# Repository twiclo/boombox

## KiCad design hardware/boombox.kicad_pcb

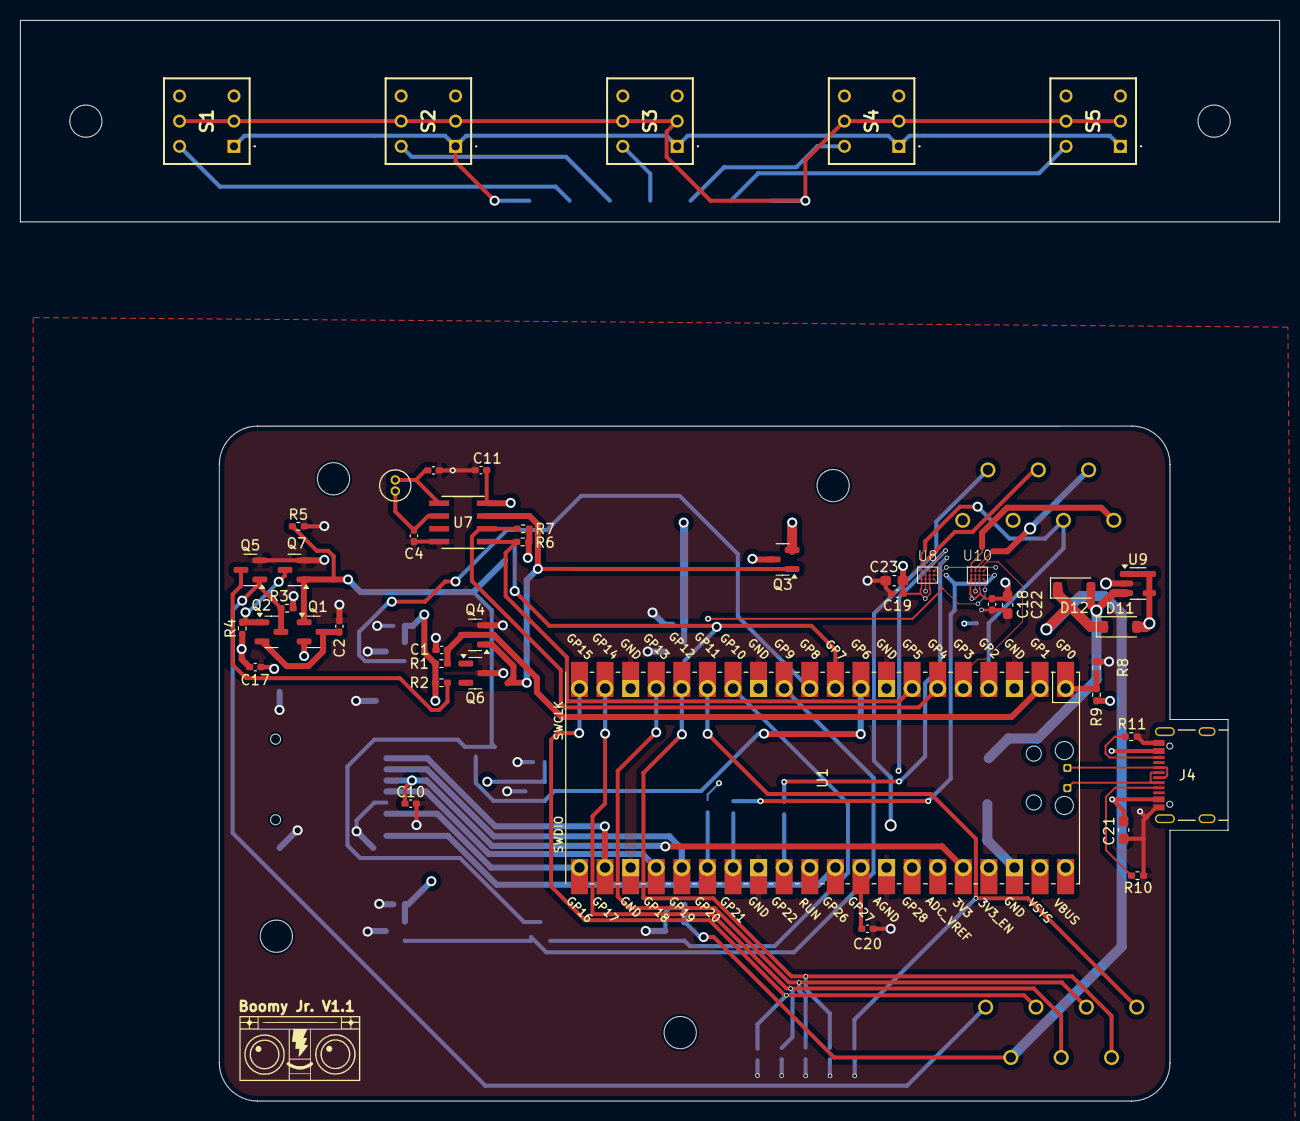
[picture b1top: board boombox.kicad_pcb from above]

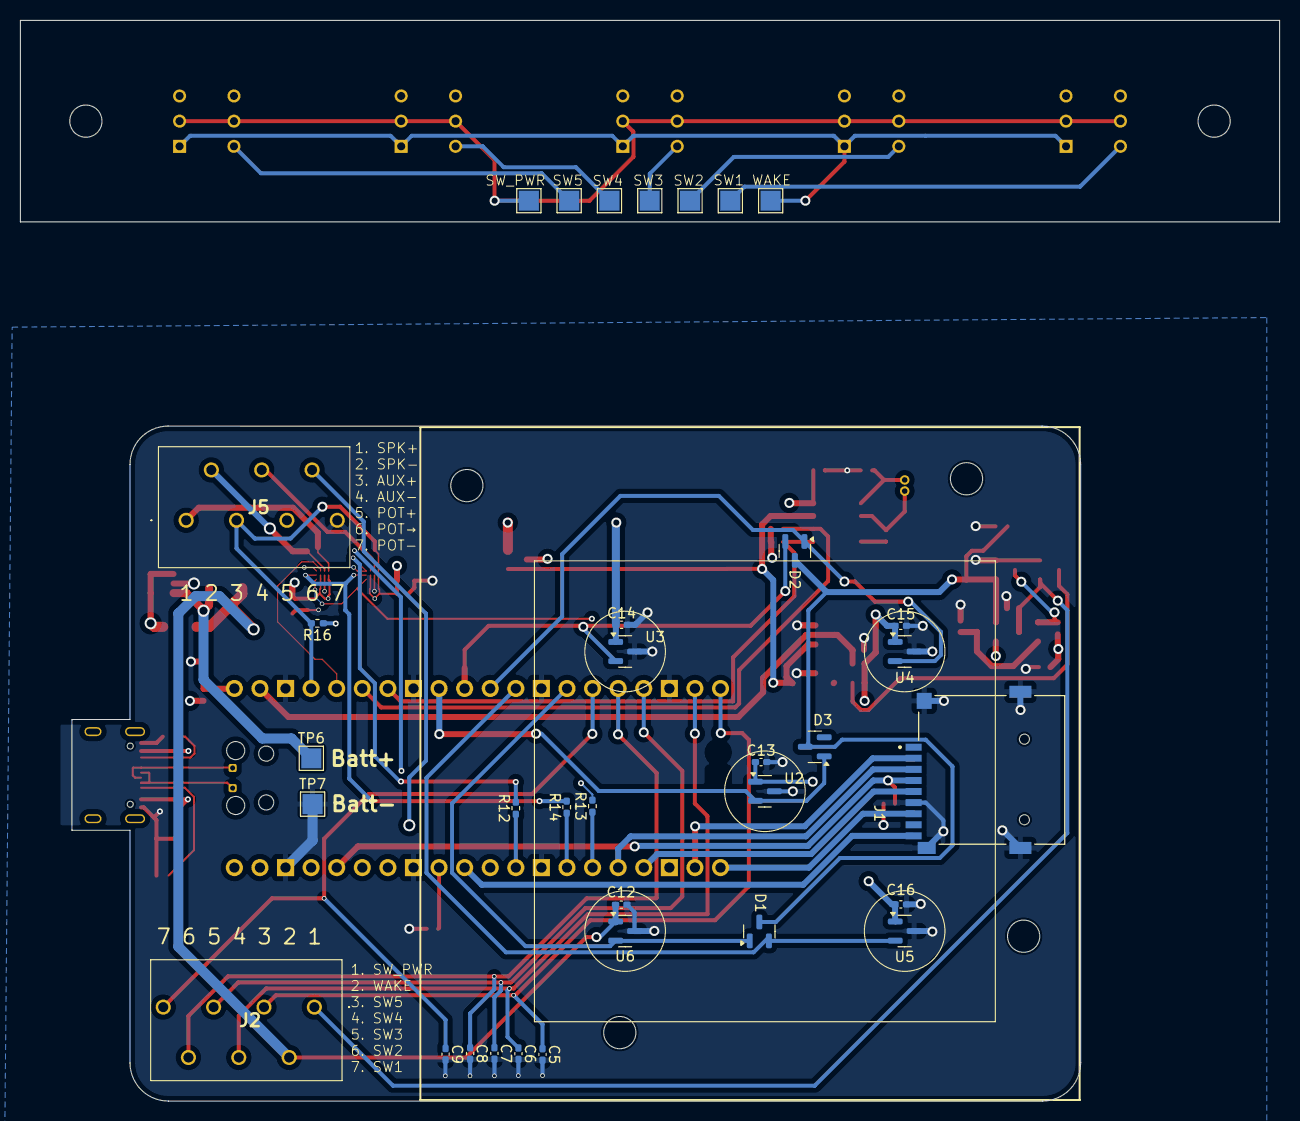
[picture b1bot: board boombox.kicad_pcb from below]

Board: 4 copper layers, 125.0 x 107.3 mm, 79 parts (34 on the bottom side), 56 nets.

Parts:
C1, C3, C4: 6pF; C_0402_1005Metric_Pad0.74x0.62mm_HandSolder
C2: 1nF; C_0402_1005Metric_Pad0.74x0.62mm_HandSolder
C5, C6, C7, C8, C9: 0.1u; C_0402_1005Metric_Pad0.74x0.62mm_HandSolder
C10, C11, C12, C13, C14, C15, C16, C17, C18, C19, C20: 0.1uF; C_0402_1005Metric_Pad0.74x0.62mm_HandSolder
C21, C22, C23: 10uF; C_0603_1608Metric_Pad1.08x0.95mm_HandSolder
D1, D2, D3: D_Dual_CommonCathode_AAK_Split; SOT-23
D11, D12: D_Schottky; D_SOD-123
J1: Micro_SD_Card_Det1; CUI_MSD-4-A
J2, J5: Screw_Terminal_01x07; 1990054
J4: USB_C_Receptacle_USB2.0_16P; CUI_UJ20-C-H-C-4-SMT-TR
Q1, Q2, Q3, Q4, Q5, Q6, Q7: SOT-23
R1, R2, R3, R4, R5, R16: 1M; R_0402_1005Metric_Pad0.72x0.64mm_HandSolder
R6, R7, R8, R9: 10k; R_0402_1005Metric_Pad0.72x0.64mm_HandSolder
R10, R11: 5.1k; R_0402_1005Metric_Pad0.72x0.64mm_HandSolder
R12, R13, R14: 0; R_0402_1005Metric_Pad0.72x0.64mm_HandSolder
S1, S2, S3, S4, S5: TL2202OAYA
TP1, TP2, TP3, TP4, TP5, TP6, TP7, TP8, TP12: TestPoint_Small; TestPoint_Pad_2.0x2.0mm
U1: Pico; RPi_Pico_SMD_TH
U2, U3, U4, U5, U6: TMAG5231; SOT-23
U7: MCP7940MT-I/SN; SOIC8-N_MC_MCH
U8, U10: MAX98365A; MAX98365
U9: MCP73811T-420I-OT; SOT-23-5
Y1: Crystal; XTAL_ECS-.327-6-13X

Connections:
/Audio/HEADPHONE_EN: U1.34 (GPIO28_ADC2), U8.A3 (EN)
/Audio/I2S_BCLK: R12.1, U1.29 (GPIO22)
/Audio/I2S_DOUT: R14.1, U1.27 (GPIO21)
/Audio/I2S_LRCLK: R13.1, U1.26 (GPIO20)
/Audio/SPEAKER_EN: U1.5 (GPIO3), U10.A3 (EN)
/Audio/VOL: C20.1, J5.6, U1.32 (GPIO27_ADC1)
/Audio/~HEADPHONE_DETECT: J5.3, R16.2, U1.4 (GPIO2), U8.A1 (OUTP)
/Power/BTN_LATCH: J2.1, Q2.3 (D), Q5.1 (G), R3.1
/Power/CLOCK_ALARM: Q3.1 (G), Q4.1 (G), Q5.3 (D), Q6.3 (D), R2.2, U7.7 (MFP)
/Power/MAG_SENSOR0: D3.1 (A), U1.9 (GPIO6), U2.2 (OUT)
/Power/MAG_SENSOR1: D2.2 (A), U1.10 (GPIO7), U3.2 (OUT)
/Power/MAG_SENSOR2: D2.1 (A), U1.11 (GPIO8), U4.2 (OUT)
/Power/MAG_SENSOR3: D1.2 (A), U1.12 (GPIO9), U5.2 (OUT)
/Power/MAG_SENSOR4: D1.1 (A), U1.14 (GPIO10), U6.2 (OUT)
/Power/POWER IN: C21.1, D11.2 (A), J4.A4 (VBUS), J4.A9 (VBUS), J4.B4 (VBUS), J4.B9 (VBUS), R9.2, U9.1 (CE), U9.4 (V_{DD}), U9.5 (PROG)
/Power/~POWER_OFF: C1.1, Q4.3 (D), Q6.1 (G), R1.2, U1.2 (GPIO1)
/USB_DN: J4.A7 (D-), J4.B7 (D-), U1.45 (DN)
/USB_DP: J4.A6 (D+), J4.B6 (D+), U1.44 (DP)
/USB_PWR_DET: R8.2, R9.1, U1.1 (GPIO0)
BTN_PWR: S1.2 (COM_1), S1.5 (COM_2), S2.2 (COM_1), S2.5 (COM_2), S3.2 (COM_1), S3.5 (COM_2), S4.2 (COM_1), S4.5 (COM_2), S5.2 (COM_1), S5.5 (COM_2), TP12.1
GND: C1.2, C2.2, C3.1, C4.1, C5.2, C6.2, C7.2, C8.2, C9.2, C10.2, C11.2, C12.2, C13.2, C14.2, C15.2, C16.2, C17.2, C18.2, C19.2, C20.2, C21.2, C22.2, C23.2, J1.6 (VSS), J1.10 (SHIELD), J4.A1 (GND), J4.A12 (GND), J4.B1 (GND), J4.B12 (GND), J5.7, Q4.2 (S), Q5.2 (S), Q6.2 (S), Q7.2 (S), R3.2, R5.2, R8.1, R10.2, R11.2, TP7.1, U1.3 (GND), U1.8 (GND), U1.13 (GND), U1.18 (GND), U1.23 (GND), U1.28 (GND), U1.33 (AGND), U1.38 (GND), U2.3 (GND), U3.3 (GND), U4.3 (GND), U5.3 (GND), U6.3 (GND), U7.4 (VSS), U8.B2 (GND), U8.C2 (GND), U9.2 (V_{SS}), U10.B2 (GND), U10.C2 (GND)
unnamed: D1.3 (K), D2.3 (K), D3.3 (K), Q1.1 (G), Q7.1 (G), R5.1
unnamed: D12.2 (A), TP6.1, U9.3 (V_{BAT})
unnamed: J1.5 (CLK), U1.24 (GPIO18)
unnamed: J1.3 (CMD), U1.25 (GPIO19)
unnamed: J1.7 (DAT0), U1.21 (GPIO16)
unnamed: J1.2 (DAT3/CD), U1.22 (GPIO17)
unnamed: J1.9 (DET), U1.31 (GPIO26_ADC0)
unnamed: C10.1, J1.4 (VDD), U1.36 (3V3)
unnamed: C5.1, J2.3, U1.20 (GPIO15)
unnamed: C6.1, J2.4, U1.19 (GPIO14)
unnamed: C7.1, J2.5, U1.17 (GPIO13)
unnamed: C8.1, J2.6, U1.16 (GPIO12)
unnamed: C9.1, J2.7, U1.15 (GPIO11)
unnamed: J4.A5 (CC1), R10.1
unnamed: J4.B5 (CC2), R11.1
unnamed: J5.1, U10.A1 (OUTP)
unnamed: J5.2, U10.A2 (OUTN)
unnamed: J5.4, U8.A2 (OUTN)
unnamed: C2.1, Q1.3 (D), Q2.2 (S)
unnamed: Q2.1 (G), Q7.3 (D), R4.2
unnamed: S1.1 (NC_1), S2.1 (NC_1), S3.1 (NC_1), S4.1 (NC_1), S5.1 (NC_1), TP8.1
unnamed: S1.4 (NC_2), TP1.1
unnamed: S2.4 (NC_2), TP2.1
unnamed: S3.4 (NC_2), TP3.1
unnamed: S4.4 (NC_2), TP4.1
unnamed: S5.4 (NC_2), TP5.1
unnamed: R7.2, U1.6 (GPIO4), U7.6 (SCL)
unnamed: R6.2, U1.7 (GPIO5), U7.5 (SDA)
unnamed: C3.2, U7.1 (X1), Y1.2
unnamed: C4.2, U7.2 (X2), Y1.1
unnamed: R13.2, U8.C4 (DAI0), U10.C4 (DAI0)
unnamed: R14.2, U8.B4 (DAI1), U10.B4 (DAI1)
unnamed: R12.2, U8.A4 (DAI2), U10.A4 (DAI2)
SLP_PWR: C11.1, C12.1, C13.1, C14.1, C15.1, C16.1, C17.1, D11.1 (K), D12.1 (K), J2.2, Q1.2 (S), Q3.2 (S), R1.1, R2.1, R4.1, U2.1 (VCC), U3.1 (VCC), U4.1 (VCC), U5.1 (VCC), U6.1 (VCC), U7.8 (VCC)
VCC: C18.1, C19.1, C22.1, C23.1, J5.5, Q3.3 (D), R6.1, R7.1, R16.1, U1.39 (VSYS), U8.B1 (PVDD), U8.B3 (GAIN_SLOT), U8.C1 (PVDD), U8.C3 (VDD), U10.B1 (PVDD), U10.B3 (GAIN_SLOT), U10.C1 (PVDD), U10.C3 (VDD)

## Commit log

2024-10-19 Almost done with schematics
2024-10-19 Imported PCB and generated errors
2024-10-22 Schematic done
2024-10-25 values
2024-10-30 Comitting so Nate can see errors
2024-11-13 Routing
2024-11-15 Gitignore
2024-11-16 Added button panel
2024-11-22 Switches
2024-11-30 Resized cartridge and moved around things
2024-11-30 Resizing
2024-12-03 Almost done TM
2024-12-03 Fixing warnings
2024-12-03 Fixed warnings
2024-12-03 Added debouncing caps
2024-12-03 Got rid of pico submodule
2024-12-03 Updated logo
2024-12-04 Rounded corners
2024-12-08 Reading from SD card
2024-12-09 Read from the first file in track1 of each cartridge
2024-12-09 Nate doesn't know how to read a file in C
2024-12-09 Valid checking of wave file
2024-12-10 Added wave file channels into mono output
2024-12-12 Flipped mosfet
2024-12-17 speaker
2024-12-18 Sound works
2024-12-19 Combine channels
2024-12-19 Won't turn off when mag gpio is initialized
2024-12-19 mag_gpio
2024-12-20 Dynamically find the data
